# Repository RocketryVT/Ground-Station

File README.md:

# Ground Station

Pico 2W-based ground station for rocket tracking. Receives telemetry via dual LoRa radios, gets ground-station GPS position from Starlink over WiFi/MQTT, and drives two differential servo axes for antenna pointing.

## Hardware Overview

| Subsystem            | Interface  | Notes                                  |
| -------------------- | ---------- | -------------------------------------- |
| LoRa 1 (SX1276)      | SPI0       | 915 MHz telemetry RX                   |
| LoRa 2 (RFM69HCW)    | SPI1       | 433 MHz backup / command link          |
| GPS (ground station) | WiFi       | Position from Starlink router via MQTT |
| Servo 1 (Zenith)     | UART0 pins | Differential step/dir driver           |
| Servo 2 (Azimuth)    | UART1 pins | Differential step/dir driver           |
| Barometer            | I2C0       | Not populated – future expansion       |
| IMU + Magnetometer   | I2C1       | Not populated – future expansion       |

---

## Pico 2W Pinout

| Phys Pin | GPIO | Signal                | Notes                           |
| -------- | ---- | --------------------- | ------------------------------- |
| 1        | 0    | Servo 1 PUL+          | UART0 TX repurposed as GPIO     |
| 2        | 1    | Servo 1 PUL−          | UART0 RX repurposed as GPIO     |
| 4        | 2    | Servo 1 DIR+          | UART0 CTS repurposed as GPIO    |
| 5        | 3    | Servo 1 DIR−          | UART0 RTS repurposed as GPIO    |
| 6        | 4    | Servo 2 PUL+          | UART1 TX repurposed as GPIO     |
| 7        | 5    | Servo 2 PUL−          | UART1 RX repurposed as GPIO     |
| 9        | 6    | Servo 2 DIR+          | UART1 CTS repurposed as GPIO    |
| 10       | 7    | Servo 2 DIR−          | UART1 RTS repurposed as GPIO    |
| 11       | 8    | LoRa1 RST             | SX1276 / 915 MHz                |
| 12       | 9    | LoRa1 G0 (DIO0 / IRQ) | SX1276 / 915 MHz                |
| 14       | 10   | LoRa1 EN              | SX1276 / 915 MHz power enable   |
| 15       | 11   | LoRa2 RST             | RFM69HCW / 433 MHz              |
| 16       | 12   | SPI1 MISO — LoRa2     | RFM69HCW / 433 MHz              |
| 17       | 13   | SPI1 CS   — LoRa2     | RFM69HCW / 433 MHz              |
| 19       | 14   | SPI1 SCK  — LoRa2     | RFM69HCW / 433 MHz              |
| 20       | 15   | SPI1 MOSI — LoRa2     | RFM69HCW / 433 MHz              |
| 21       | 16   | I2C0 SDA              | Not populated (Barometer)       |
| 22       | 17   | I2C0 SCL              | Not populated (Barometer)       |
| 24       | 18   | SPI0 SCK  — LoRa1     | SX1276 / 915 MHz                |
| 25       | 19   | SPI0 MOSI — LoRa1     | SX1276 / 915 MHz                |
| 26       | 20   | SPI0 MISO — LoRa1     | SX1276 / 915 MHz                |
| 27       | 21   | SPI0 CS   — LoRa1     | SX1276 / 915 MHz                |
| 29       | 22   | LoRa2 G0 (DIO0 / IRQ) | RFM69HCW / 433 MHz              |
| 31       | 26   | I2C1 SDA              | Not populated (IMU / Mag)       |
| 32       | 27   | I2C1 SCL              | Not populated (IMU / Mag)       |
| 34       | 28   | LoRa2 EN              | RFM69HCW / 433 MHz power enable |

---

## Servo Connector Pinout

Each servo driver expects differential step/direction signals (e.g. RS-422 / open-collector driver).

| Signal | Servo 1 (Zenith) GPIO | Servo 2 (Azimuth) GPIO | JST Pin |
| ------ | --------------------- | ---------------------- | ------- |
| PUL+   | 0                     | 4                      | 1       |
| PUL−   | 1                     | 5                      | 2       |
| DIR+   | 2                     | 6                      | 3       |
| DIR−   | 3                     | 7                      | 4       |

---

## LoRa Module Connector Pinout

Both LoRa headers share the same signal ordering. SPI bus differs per module.

| Signal | LoRa1 (SX1276 / 915 MHz) | LoRa2 (RFM69HCW / 433 MHz) | JST Pin |
| ------ | ------------------------ | -------------------------- | ------- |
| EN     | GPIO 10                  | GPIO 28                    | 1       |
| G0     | GPIO 9                   | GPIO 22                    | 2       |
| SCK    | GPIO 18 (SPI0)           | GPIO 14 (SPI1)             | 3       |
| MISO   | GPIO 20 (SPI0)           | GPIO 12 (SPI1)             | 4       |
| MOSI   | GPIO 19 (SPI0)           | GPIO 15 (SPI1)             | 5       |
| CS     | GPIO 21 (SPI0)           | GPIO 13 (SPI1)             | 6       |
| RST    | GPIO 8                   | GPIO 11                    | 7       |
| GND    | —                        | —                          | 8       |
| 3V3    | —                        | —                          | 9       |

---

## I2C Headers (not populated)

| Bus  | SDA     | SCL     | Planned Devices   |
| ---- | ------- | ------- | ----------------- |
| I2C0 | GPIO 16 | GPIO 17 | Barometer         |
| I2C1 | GPIO 26 | GPIO 27 | IMU, Magnetometer |

---

## GPS

Ground-station position is obtained from a Starlink router over WiFi. No dedicated UART/GPIO pins are used. The Pico 2W connects to the router SSID and subscribes to a GPS MQTT topic (`gs/gps`).

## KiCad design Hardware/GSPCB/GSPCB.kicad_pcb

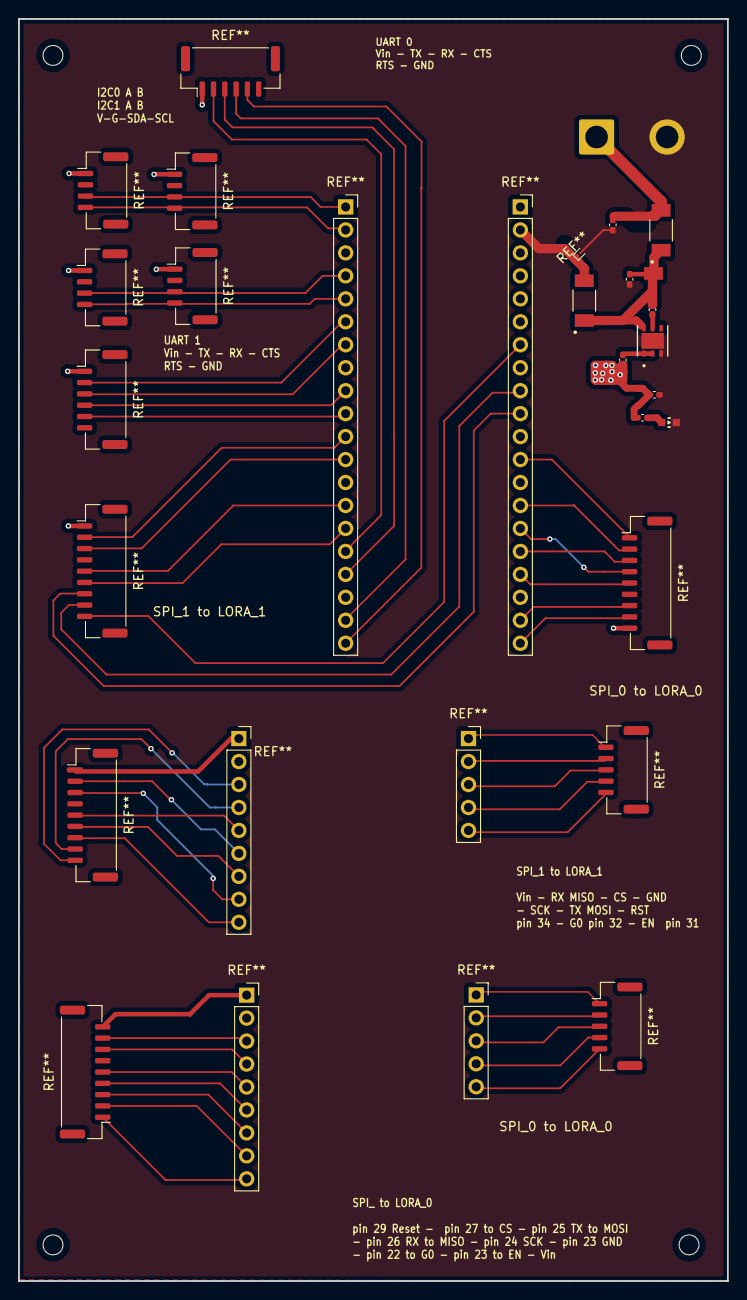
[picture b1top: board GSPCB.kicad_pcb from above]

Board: 2 copper layers, 78.4 x 139.6 mm, 15 parts (0 on the bottom side), 7 nets.

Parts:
C15, C16, C21: 10uF; C_0402_1005Metric_Pad0.74x0.62mm_HandSolder
D3, D4: PMEG3050EP_115; DIO_PMEG3050EP_115
D11: WL-SMCW_0603
H2, H2#2, H2#3, H2#4: MountingHole; MountingHole_2.2mm_M2
J2: Conn_01x02_Socket; SolderWire-2sqmm_1x02_P7.8mm_D2mm_OD3.9mm
R4: 100k; C_0402_1005Metric_Pad0.74x0.62mm_HandSolder
R15: 100; C_0402_1005Metric_Pad0.74x0.62mm_HandSolder
R21: 0; C_0402_1005Metric_Pad0.74x0.62mm_HandSolder
U4: LD39200PU33R; SON_DFN6_3X3_STM-L

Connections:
/VBATT: C21.1, D3.A, J2.1
/VREG_3V3: C16.1, R15.1, R21.2
GND: C15.2, C16.2, C21.2, D11.1, J2.2, U4.3 (GND), U4.7 (GND)
unnamed: D11.2, R15.2
unnamed: R21.1, U4.1 (OUT), U4.2 (ADJ/SENSE)
unnamed: R4.2, U4.5 (EN)
unnamed: C15.1, D3.K, D4.K, R4.1, U4.6 (IN)

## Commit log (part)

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2024-07-17 added raylib at 5.0 release
2024-07-17 Compiles example project, works on M1 MacOS
2024-07-17 Create cmake-multi-platform.yml
    Testing out suggested workflow.
2024-07-17 Fixed CMakeLists typo
2024-07-17 Added submodule recursive to github workflow repo checkout
2024-07-17 Added install for libxrandr-dev on ubuntu
2024-07-17 Updated workflow to archive binaries
2024-07-17 Updated windows archive path and added more missing dependies for ubuntu builds
2024-07-17 Updated windows archive path again and added directory printout to help debug my archive issues
2024-07-18 Updated to use macos runner and adjusted windows directory printout
2024-07-18 Updated workflow to remove deplicate compiler runs
2024-07-18 changed binary name to maybe stop windows from flagging it as a virus
2024-07-18 Changed the workflow to archive the whole bin folder so executables aren't hardcoded
2024-07-18 Fixed chmod step in workflow
2025-11-16 added blinking example for rp2350 with freertos
2025-11-27 Moved QT to gui folder
2025-11-27 added gitignore
2025-11-27 Fixed readme name
2025-11-28 Removed duplicate readme
2026-02-01 Three.js ground station
2026-02-08 Revert "Three.js ground station"
    This reverts commit 64947b32be7c1c7e0128e08cef5c645c22ffa7ae.
2026-02-08 Added gui2 and pico intro
2026-02-26 removed broken files
2026-02-28 New Ground Station
2026-02-28 Having issues with Lora
2026-03-12 GSPCB kicad upload 3/12
2026-03-18 New Ground Station using CesiumJS + React + ThreeJS, with python logger
2026-03-18 Make sure you have a mostquitto broker setup and then call: mosquitto_sub -h 192.168.8.171 -t gs/demo
    {"count":97,"uptime_ms":115609}
    {"count":98,"uptime_ms":116609}
    {"count":99,"uptime_ms":117609}
    {"count":100,"uptime_ms":118609}
    {"count":101,"uptime_ms":119609}
    {"count":102,"uptime_ms":120609}
2026-03-30 updated but needs work
2026-04-10 work in progress ground station firmware
2026-04-10 work in progress ground station interface
2026-04-12 Current Version, pre final updates
    uses ground and power planes, pre condensation and added circuitry
2026-04-16 nearly final version
    added lvl shfter, 5v reg, changed a bunch
2026-04-16 Final Iteration Pending Design Check
2026-04-20 Final board GSPCB
2026-04-26 Quick touchups and final review for ordering, needs BoM confirmation
    - Rerouted a couple signal lines on bottom layer for spacing and groundplane placement
    - Touched up a few copper pour boundaries for simplified component placement
    - Added more silkscreen labels and aligned with components, including I2C port pinout
    - Standardized (larger) vias for JLCPCB ordering
2026-04-28 Final Rev1 ordered 4/27/26
2026-05-22 raw sensor visualizatations
2026-05-22 updated mqtt topics
2026-05-22 removed unused servo pins
2026-05-22 servo supports absoulte 0-360 deg commands
2026-05-22 fixed different video aspect ratios hiding device drop down menu
2026-06-03 updated web ui and pico file for servos
2026-06-03 Switched from JSON to protobuf for MQTT
2026-06-05 tauri ground station rewrite
2026-06-05 Moved to tauri gs and updated protobuf files
2026-06-05 Updated ground station tracking to have proper calibration process and a better stepper control loop using imu for reference syncing
2026-06-06 Updated calibartion
2026-06-06 Hard and soft iron wizard
2026-06-06 Newer visualization for orientation
2026-06-06 removed older ground station
2026-06-06 Improved rocket visualization and at
2026-06-13 GS updated 3d AT model
2026-06-16 Updated GS and SubGS
2026-06-16 Updated setSyncWord
2026-06-17 updated ground station
2026-06-17 removed build files
